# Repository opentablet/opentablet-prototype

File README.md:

# opentablet

A small drawing-tablet like input device with high (1kHz) polling rates and low latency, designed to be compatible with a small number of Wacom pens. Only supports position tracking, not clicking or pen pressure.

This version was an early prototype. The analog front end has several shortcomings (noisy and limited range) and is overly complex for its intended task. Next version should solve these issues.

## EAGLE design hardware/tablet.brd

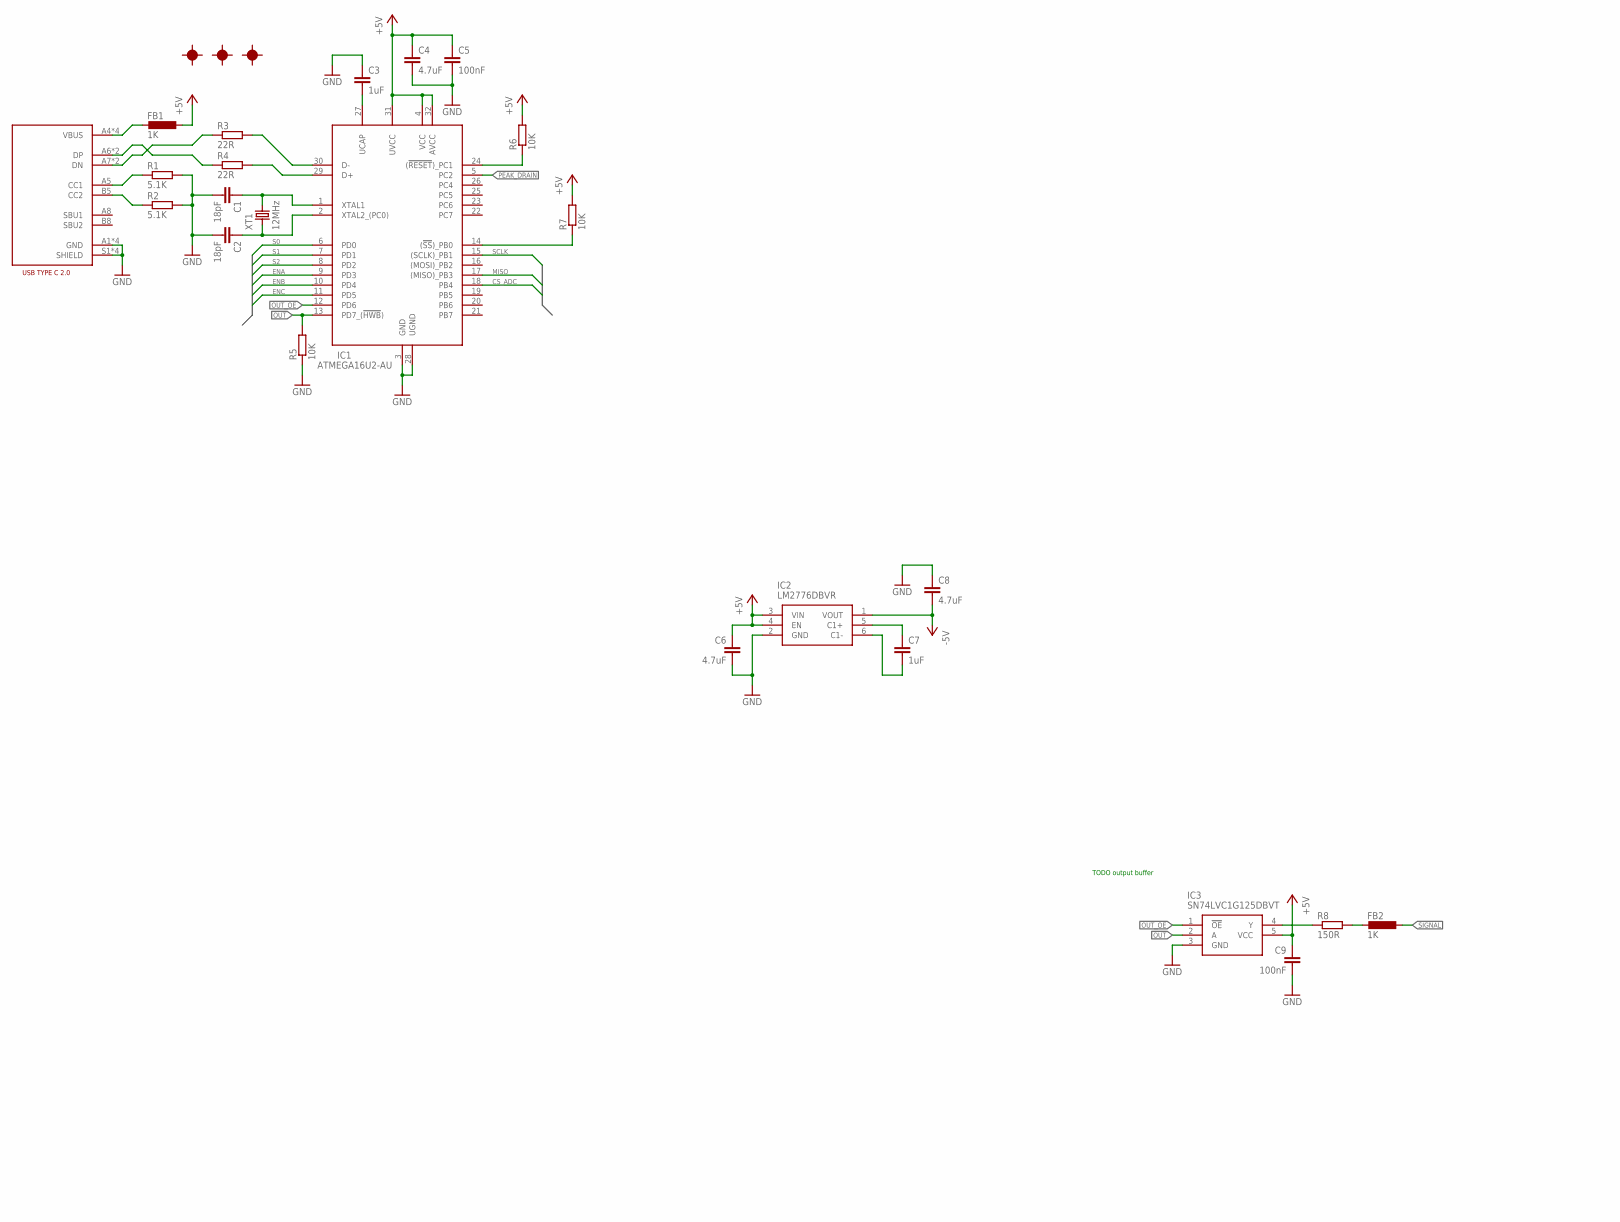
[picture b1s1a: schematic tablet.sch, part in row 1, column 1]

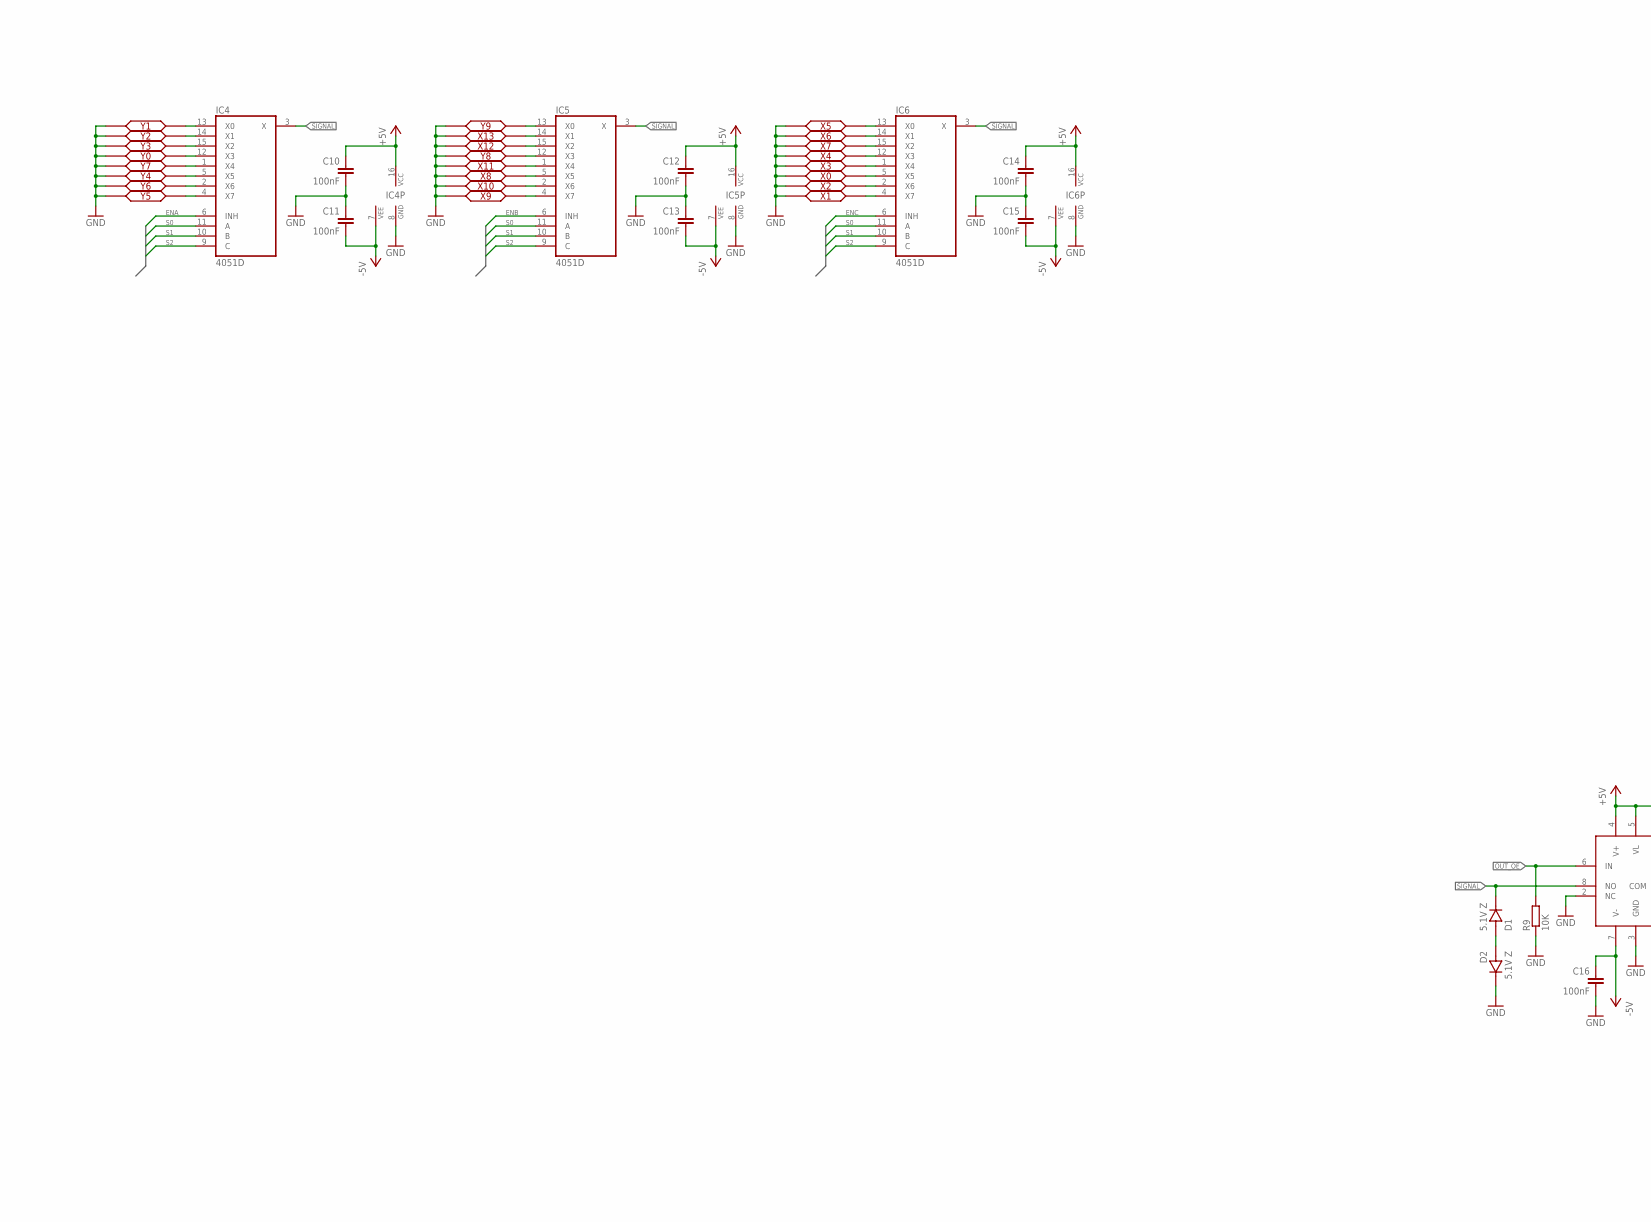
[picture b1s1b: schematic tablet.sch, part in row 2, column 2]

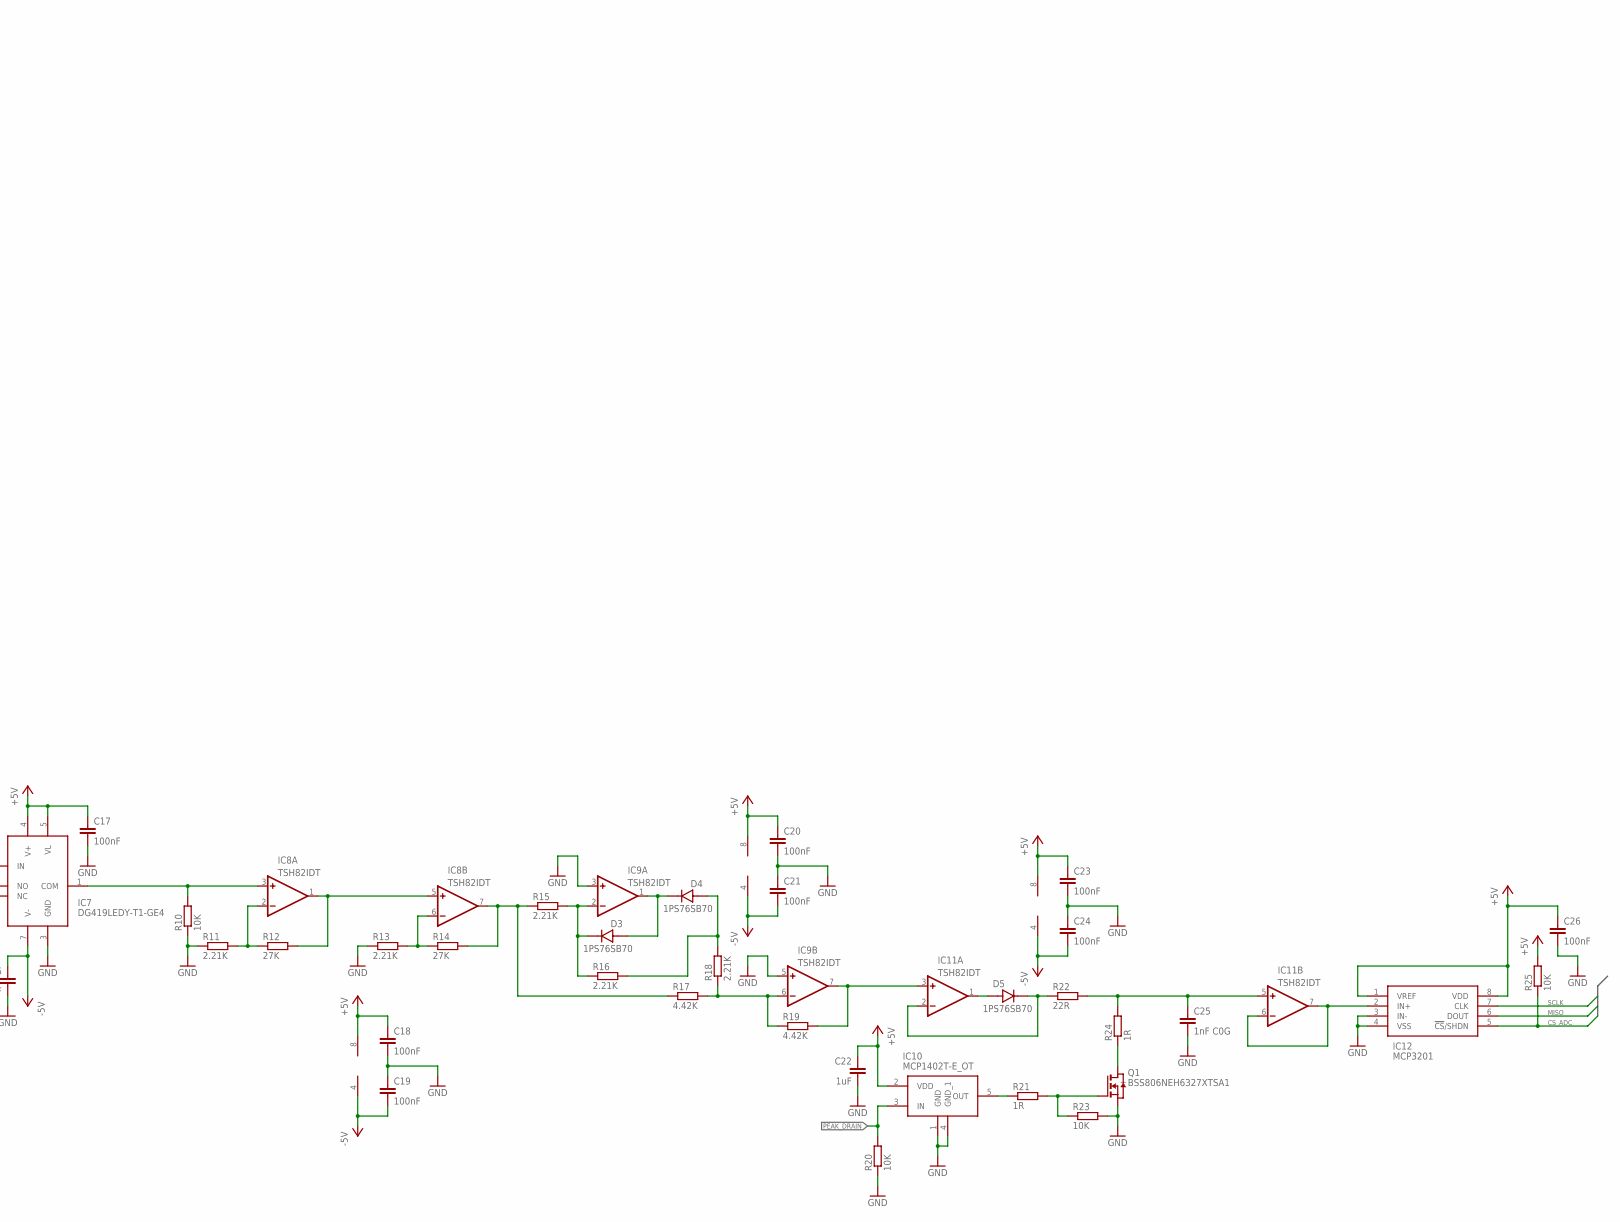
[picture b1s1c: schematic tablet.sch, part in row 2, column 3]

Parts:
C1, C2: 18pF; 0805
C3, C7, C22: 1uF; 0805
C4, C6, C8: 4.7uF; 0805
C5, C9, C10, C11, C12, C13, C14, C15, C16, C17, C18, C19, C20, C21, C23, C24, C26: 100nF; 0805
C25: 1nF C0G; 0805
D1, D2: 5.1V Z; SOD323
D3, D4, D5: 1PS76SB70; SOD323
FB1, FB2: 1K; 0805
FD1, FD2, FD3: FIDUCIAL1_2; FIDUCIAL
IC1: ATMEGA16U2-AU; QFP80P900X900X120-32N
IC2: LM2776DBVR; SOT95P280X145-6N
IC3: SN74LVC1G125DBVT; SOT95P280X145-5N
IC4, IC5, IC6: 4051D; SO16
IC7: DG419LEDY-T1-GE4; SOIC8
IC8, IC9, IC11: TSH82IDT; SOIC8
IC10: MCP1402T-E_OT; SOT95P270X145-5N
IC12: MCP3201; SOIC8
J1: USB4085-GF-A
Q1: BSS806NEH6327XTSA1; SOT23_3
R1, R2: 5.1K; 0805
R3, R4, R22: 22R; 0805
R5, R6, R7, R9, R10, R20, R23, R25: 10K; 0805
R8: 150R; 0805
R11, R13, R15, R16, R18: 2.21K; 0805
R12, R14: 27K; 0805
R17, R19: 4.42K; 0805
R21, R24: 1R; 0805
X0, X1, X2, X3, X4, X5, X6, X7, X8, X9, X10, X11, X12, X13: 2P
XT1: 12MHz; HC49UP
Y0, Y1, Y2, Y3, Y4, Y5, Y6, Y7, Y8, Y9: 2P

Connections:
+5V: C4.1, C5.1, C6.1, C9.1, C10.1, C12.1, C14.1, C17.1, C18.1, C20.1, C22.1, C23.1, C26.1, FB1.1, IC1.4 (VCC), IC1.31 (UVCC), IC1.32 (AVCC), IC2.3 (VIN), IC2.4 (EN), IC3.5 (VCC), IC4.16 (VCC), IC5.16 (VCC), IC6.16 (VCC), IC7.4 (V+), IC7.5 (VL), IC8.8 (V+), IC9.8 (V+), IC10.2 (VDD), IC11.8 (V+), IC12.1 (VREF), IC12.8 (VDD), R6.2, R7.2, R25.2
-5V: C8.2, C11.2, C13.2, C15.2, C16.1, C19.2, C21.2, C24.2, IC2.1 (VOUT), IC4.7 (VEE), IC5.7 (VEE), IC6.7 (VEE), IC7.7 (V-), IC8.4 (V-), IC9.4 (V-), IC11.4 (V-)
CS_ADC: IC1.18 (PB4), IC12.5 (!CS!/SHDN), R25.1
ENA: IC1.9 (PD3), IC4.6 (INH)
ENB: IC1.10 (PD4), IC5.6 (INH)
ENC: IC1.11 (PD5), IC6.6 (INH)
GND: C1.2, C2.2, C3.1, C4.2, C5.2, C6.2, C8.1, C9.2, C10.2, C11.1, C12.2, C13.1, C14.2, C15.1, C16.2, C17.2, C18.2, C19.1, C20.2, C21.1, C22.2, C23.2, C24.1, C25.2, C26.2, D2.2, IC1.3 (GND), IC1.28 (UGND), IC2.2 (GND), IC3.3 (GND), IC4.8 (GND), IC5.8 (GND), IC6.8 (GND), IC7.2 (NC), IC7.3 (GND), IC9.3 (+IN), IC9.5 (+IN), IC10.1 (GND), IC10.4 (GND_1), IC12.3 (IN-), IC12.4 (VSS), J1.A1 (GND), J1.A12 (GND), J1.B1 (GND), J1.B12 (GND), J1.S1 (SHIELD), J1.S2 (SHIELD), J1.S3 (SHIELD), J1.S4 (SHIELD), Q1.P$2 (S), R1.2, R2.2, R5.1, R9.1, R10.1, R11.1, R13.1, R20.1, R23.2, X0.2, X1.2, X2.2, X3.2, X4.2, X5.2, X6.2, X7.2, X8.2, X9.2, X10.2, X11.2, X12.2, X13.2, Y0.2, Y1.2, Y2.2, Y3.2, Y4.2, Y5.2, Y6.2, Y7.2, Y8.2, Y9.2
MISO: IC1.17 ((MISO)_PB3), IC12.6 (DOUT)
unnamed: C1.1, IC1.1 (XTAL1), XT1.2
unnamed: D1.1, D2.1
unnamed: IC3.4 (Y), R8.1
unnamed: IC8.2 (-IN), R11.2, R12.1
unnamed: C25.1, IC11.5 (+IN), R22.2, R24.2
unnamed: C3.2, IC1.27 (UCAP)
unnamed: C2.1, IC1.2 (XTAL2_(PC0)), XT1.1
unnamed: FB1.2, J1.A4 (VBUS), J1.A9 (VBUS), J1.B4 (VBUS), J1.B9 (VBUS)
unnamed: IC8.7 (OUT), R14.2, R15.1, R17.1
unnamed: IC8.1 (OUT), IC8.5 (+IN), R12.2
unnamed: D3.2, IC9.2 (-IN), R15.2, R16.1
unnamed: J1.A5 (CC1), R1.1
unnamed: IC8.6 (-IN), R13.2, R14.1
unnamed: J1.B5 (CC2), R2.1
unnamed: D3.1, D4.2, IC9.1 (OUT)
unnamed: D4.1, R16.2, R18.2
unnamed: IC9.6 (-IN), R17.2, R18.1, R19.1
unnamed: Q1.P$1 (G), R21.2, R23.1
unnamed: D5.1, IC11.1 (OUT)
unnamed: IC9.7 (OUT), IC11.3 (+IN), R19.2
unnamed: D5.2, IC11.2 (-IN), R22.1
unnamed: IC1.14 ((!SS!)_PB0), R7.1
unnamed: IC1.24 ((!RESET!)_PC1), R6.1
unnamed: IC11.6 (-IN), IC11.7 (OUT), IC12.2 (IN+)
unnamed: IC1.29 (D+), R4.2
unnamed: IC7.1 (COM), IC8.3 (+IN), R10.2
unnamed: IC1.30 (D-), R3.2
unnamed: J1.A7 (DN), J1.B7 (DN), R3.1
unnamed: J1.A6 (DP), J1.B6 (DP), R4.1
unnamed: Q1.P$3 (D), R24.1
unnamed: IC10.5 (OUT), R21.1
unnamed: C7.1, IC2.5 (C1+)
unnamed: C7.2, IC2.6 (C1-)
unnamed: FB2.2, R8.2
OUT: IC1.13 (PD7_(!HWB!)), IC3.2 (A), R5.2
OUT_OE: IC1.12 (PD6), IC3.1 (!OE), IC7.6 (IN), R9.2
PEAK_DRAIN: IC1.5 (PC2), IC10.3 (IN), R20.2
S0: IC1.6 (PD0), IC4.11 (A), IC5.11 (A), IC6.11 (A)
S1: IC1.7 (PD1), IC4.10 (B), IC5.10 (B), IC6.10 (B)
S2: IC1.8 (PD2), IC4.9 (C), IC5.9 (C), IC6.9 (C)
SCLK: IC1.15 ((SCLK)_PB1), IC12.7 (CLK)
SIGNAL: D1.2, FB2.1, IC4.3 (X), IC5.3 (X), IC6.3 (X), IC7.8 (NO)
X0: IC6.5 (X5), X0.1
X1: IC6.4 (X7), X1.1
X2: IC6.2 (X6), X2.1
X3: IC6.1 (X4), X3.1
X4: IC6.12 (X3), X4.1
X5: IC6.13 (X0), X5.1
X6: IC6.14 (X1), X6.1
X7: IC6.15 (X2), X7.1
X8: IC5.5 (X5), X8.1
X9: IC5.4 (X7), X9.1
X10: IC5.2 (X6), X10.1
X11: IC5.1 (X4), X11.1
X12: IC5.15 (X2), X12.1
X13: IC5.14 (X1), X13.1
Y0: IC4.12 (X3), Y0.1
Y1: IC4.13 (X0), Y1.1
Y2: IC4.14 (X1), Y2.1
Y3: IC4.15 (X2), Y3.1
Y4: IC4.5 (X5), Y4.1
Y5: IC4.4 (X7), Y5.1
Y6: IC4.2 (X6), Y6.1
Y7: IC4.1 (X4), Y7.1
Y8: IC5.12 (X3), Y8.1
Y9: IC5.13 (X0), Y9.1

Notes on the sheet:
TODO output buffer

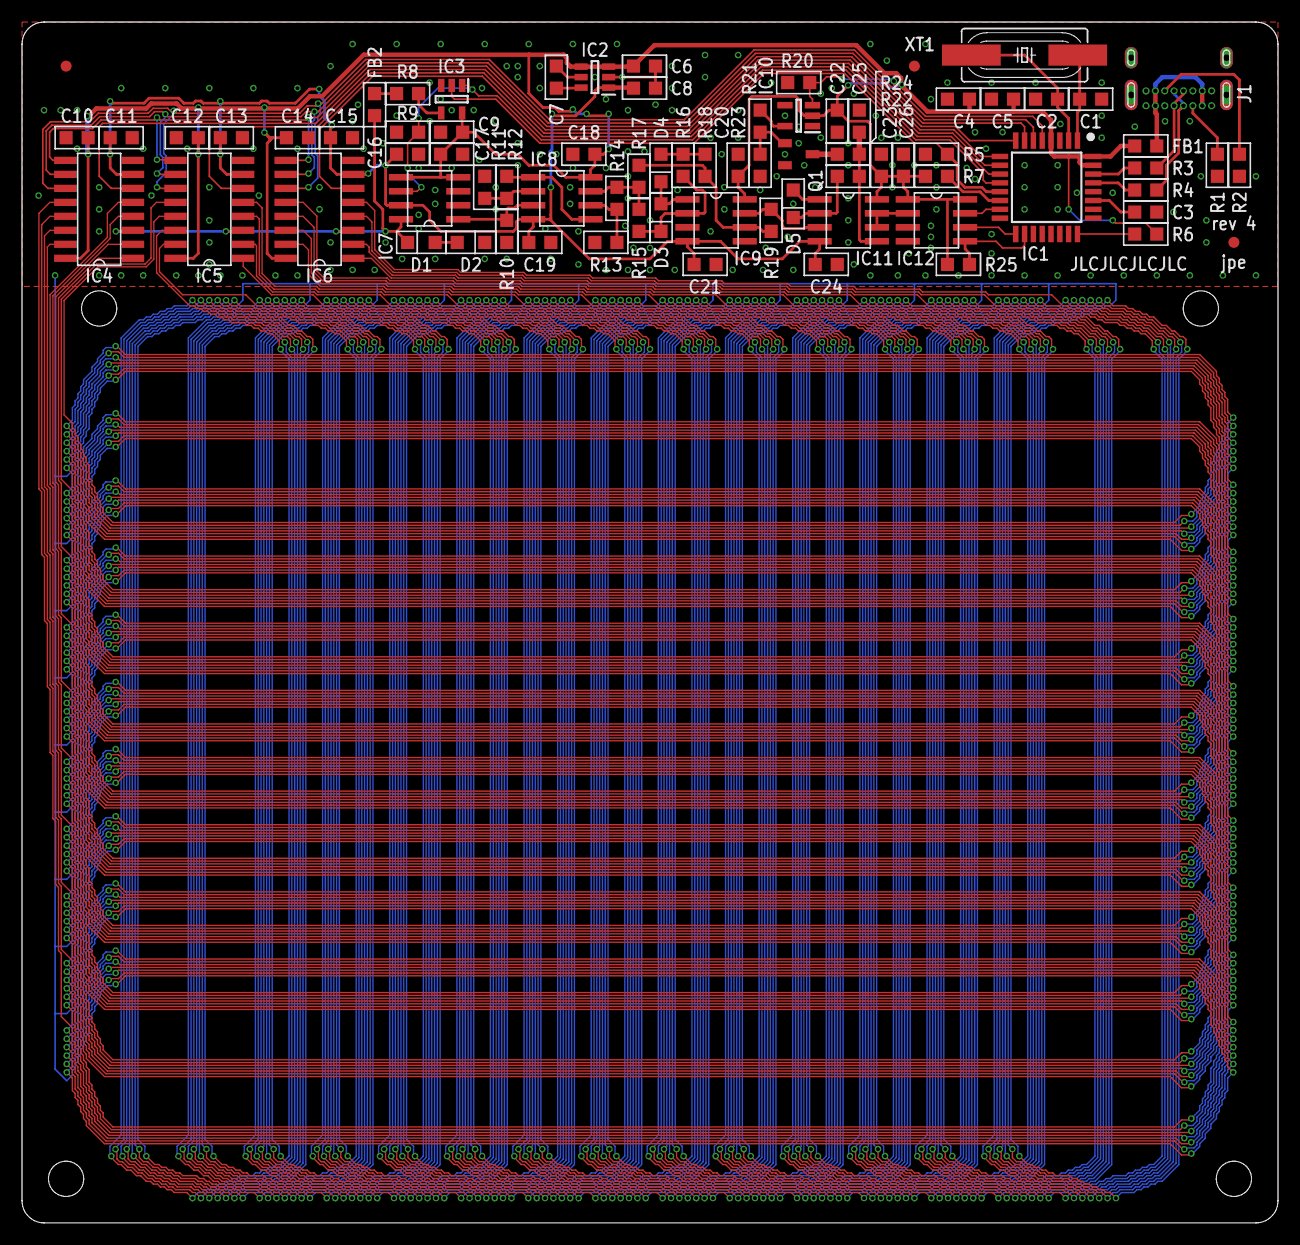
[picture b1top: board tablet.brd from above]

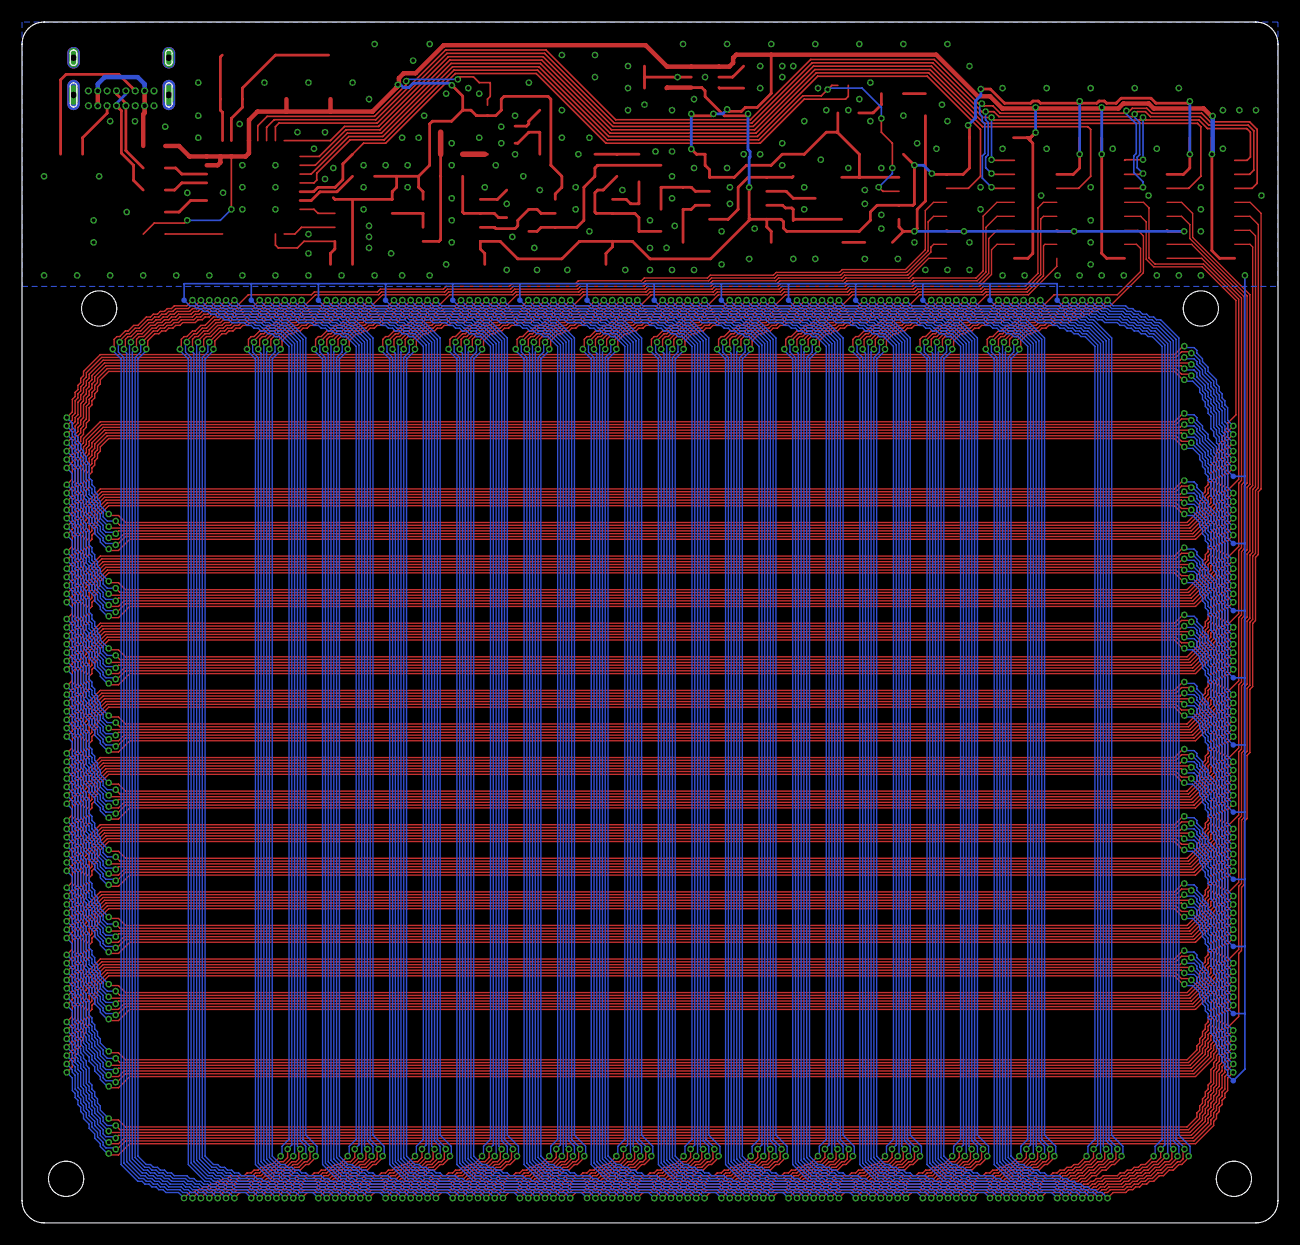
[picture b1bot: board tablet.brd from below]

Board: 2 copper layers, 114.0 x 109.0 mm, 100 parts (24 on the bottom side), 74 nets.

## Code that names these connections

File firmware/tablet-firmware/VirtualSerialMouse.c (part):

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 *  the demo and is responsible for the initial application hardware configuration.
 */

#define S0 _BV(PD0)
#define S1 _BV(PD1)
#define S2 _BV(PD2)
#define OEA _BV(PD3)
#define OEB _BV(PD4)
#define OEC _BV(PD5)
#define OUT_OE _BV(PD6)
#define OUT _BV(PD7)

#define CS_ADC _BV(PB4)

#define PEAK_DRAIN _BV(PC2)

#define COLUMNS 14
#define ROWS 10
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	SetupHardware();
	GlobalInterruptEnable();

	DDRB |= _BV(PB0) | _BV(PB1) | _BV(PB2) | CS_ADC;
	PORTB |= _BV(PB4);
	PORTB &= ~(_BV(PB1) | _BV(PB2));
	PORTB |= _BV(PB0);
	//_delay_us(10);
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
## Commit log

2022-04-18 Add .gitignore
2022-04-18 Add schematic and board layout
2022-04-18 Add firmware
2022-04-18 Add readme

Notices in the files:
firmware/tablet-firmware/VirtualSerialMouse.c:
Copyright (C) Dean Camera, 2017.
Copyright 2017  Dean Camera (dean [at] fourwalledcubicle [dot] com)
